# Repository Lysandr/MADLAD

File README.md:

# MADLAD
Modular Algorithm Demonstration Linux Autonomous Drone (MADLAD)

## What is this?
This is meant to be an open-source drone guidance, navigation, and control platform. The board is equipped with an MPU9260 (3ax accel, 3ax gyro, 3ax mag)
as well as an IMU380ZA, a single source time-of-flight lidar, and a barometer.  It has onboard 3.3V and 5V DC/DC converters. The brain is a
pocketbeagle computer.

Upgrades will be considered at a later time, this project is currently in a get-shit-done-asap stage.

## Goals for this project
* Get the flight computer board functioning.
* Get the PREEMPT_RT thread patch functioning in debian on the pocketbeagle
* Get a decent GNC framework implemented for plug and play algorithms based on a globally defined state machine

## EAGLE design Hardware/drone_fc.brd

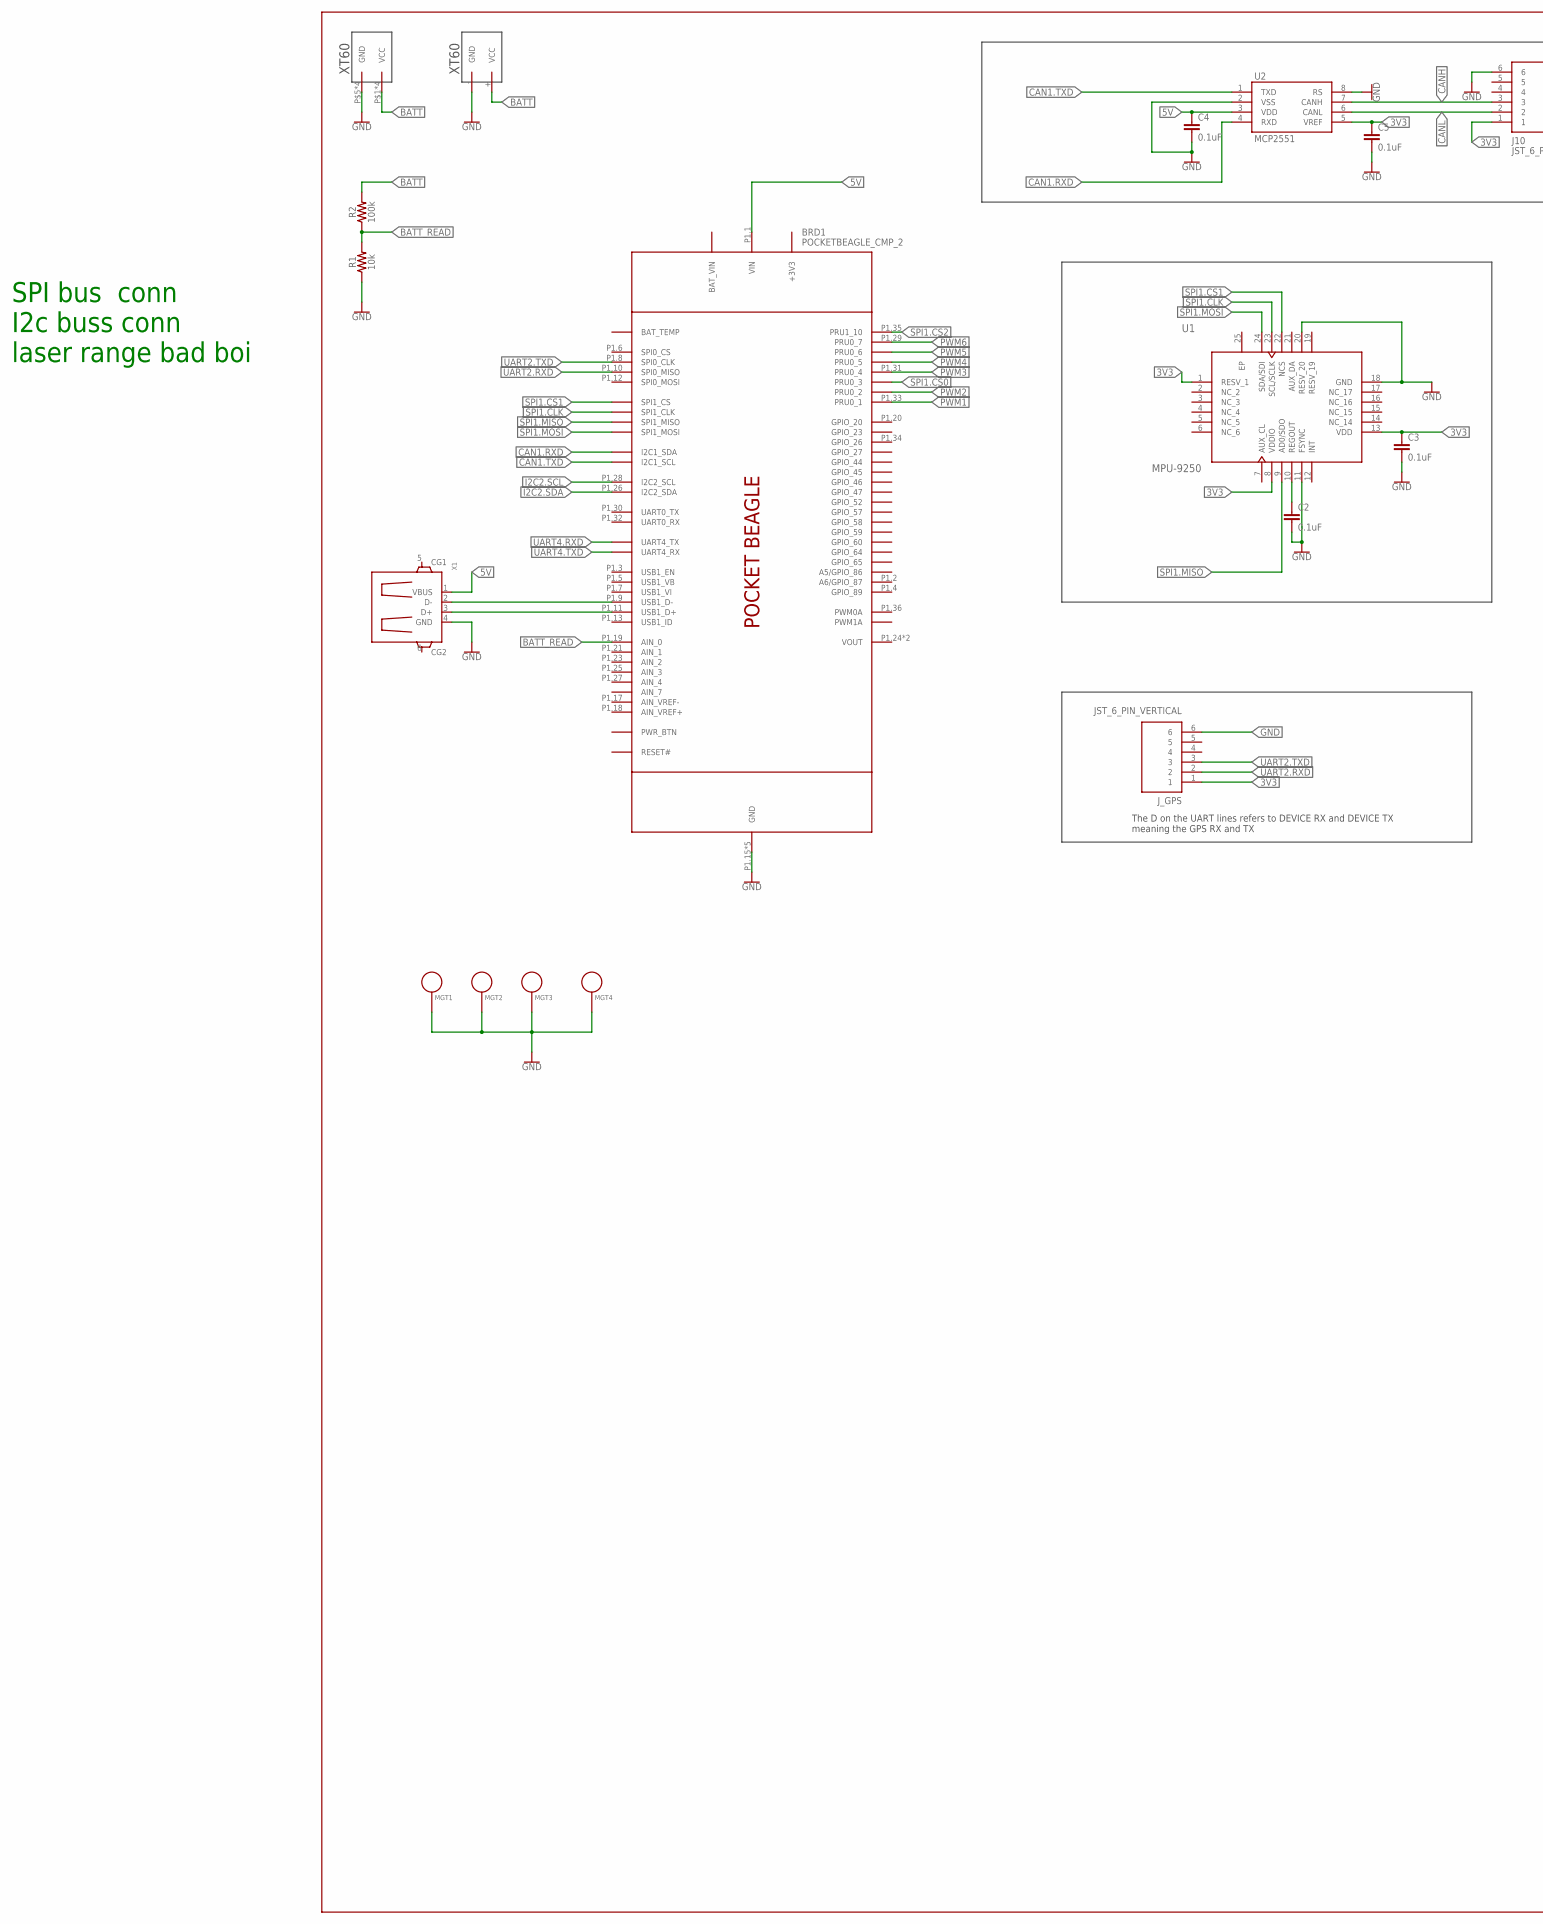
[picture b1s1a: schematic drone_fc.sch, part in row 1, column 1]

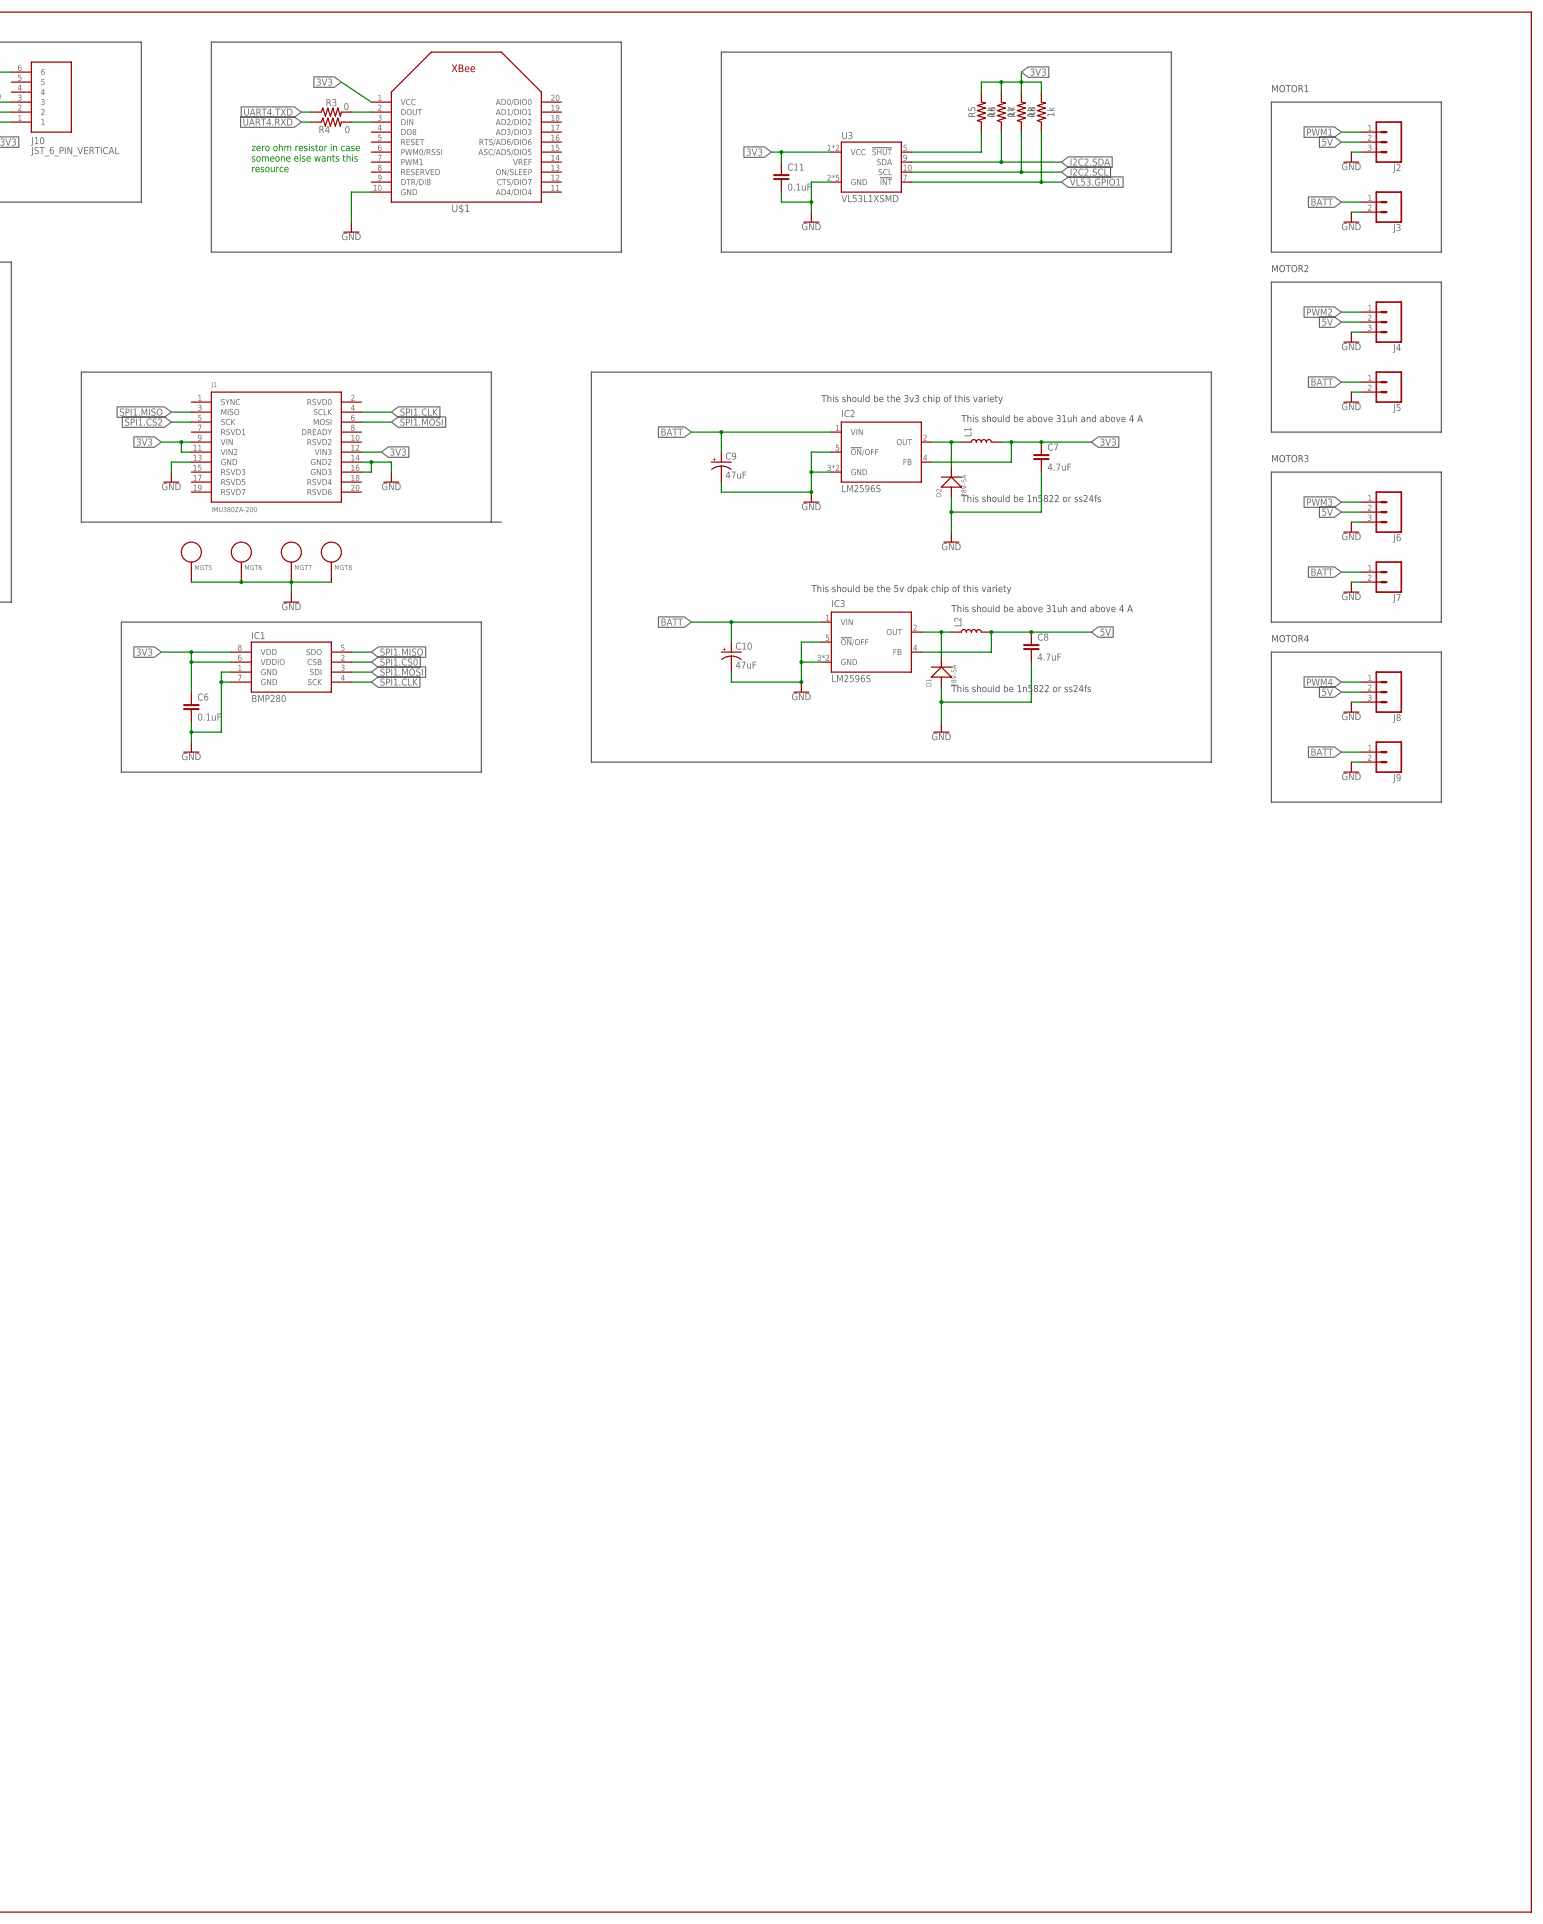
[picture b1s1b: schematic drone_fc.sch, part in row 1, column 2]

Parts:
BRD1: POCKETBEAGLE_CMP_2; POCKETBEAGLE_CMP
C2, C3, C4, C5, C6, C11: 0.1uF; 0603
C7, C8: 4.7uF; 1206
C9, C10: 47uF; PANASONIC_D
D1, D2: 28V-5A; DO-214AA
IC1: BMP280
IC2, IC3: LM2596S; TO263-5
J1: IMU380ZA-200; IMU380-CLM-110-02
J2, J4, J6, J8: CONN_03; 1X03
J3, J5, J7, J9: CONN_02PTH3; 1X02_LONGPADS
J10: JST_6_PIN_VERTICAL; JST-6-SMD-VERT-1.0MM
J_GPS: JST_6_PIN_VERTICAL; JST-6-SMD-VERT-1.0MM
L1, L2: 47µH/±30%/750mA; CR54
MGT1, MGT2, MGT3, MGT4, MGT5, MGT6, MGT7, MGT8: MOUNTING_HOLE; BEAGLEBONEBLACK_MOUNTING_HOLE
R1: 10k; 0603
R2: 100k; 0603
R3, R4: 0; 0603
R5, R6, R7, R8: 1k; 0603
U1: MPU-9250; 24-QFN
U2: MCP2551; SO08
U3: VL53L1XSMD; VL53L1X
U$1: XBEE
U$2: XT60_RA
U$3: XT60
X1: GHI2_USB_HOST_W/CHASSIS_GND; GHI2_USB_HOST_HORIZONTAL_W/CHASSIS_GND

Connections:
3V3: C3.1, C5.1, C6.1, C7.1, C11.1, IC1.6 (VDDIO), IC1.8 (VDD), IC2.4 (FB), J1.9 (VIN), J1.11 (VIN2), J1.12 (VIN3), J10.1, J_GPS.1, L1.P$2 (2), R5.2, R6.2, R7.2, R8.2, U1.1 (RESV_1), U1.8 (VDDIO), U1.13 (VDD), U2.5 (VREF), U3.1 (VCC), U3.11 (VCC), U$1.1 (VCC)
5V: BRD1.P1.1 (VIN), C4.1, C8.1, IC3.4 (FB), J2.2, J4.2, J6.2, J8.2, L2.P$2 (2), U2.3 (VDD), X1.1 (VBUS)
BATT: C9.+, C10.+, IC2.1 (VIN), IC3.1 (VIN), J3.1, J5.1, J7.1, J9.1, R2.2, U$2.P$1 (VCC), U$2.P$2 (VCC), U$2.P$3 (VCC), U$2.P$4 (VCC), U$3.+ (VCC)
BATT_READ: BRD1.P1.19 (AIN_0), R1.2, R2.1
CAN1.RXD: BRD1.P2.11 (I2C1_SDA), U2.4 (RXD)
CAN1.TXD: BRD1.P2.9 (I2C1_SCL), U2.1 (TXD)
CANH: J10.3, U2.7 (CANH)
CANL: J10.2, U2.6 (CANL)
EP: U1.25 (EP)
GND: BRD1.P1.15 (GND), BRD1.P1.16 (GND), BRD1.P1.22 (GND), BRD1.P2.15 (GND), BRD1.P2.21 (GND), C2.2, C3.2, C4.2, C5.2, C6.2, C7.2, C8.2, C9.-, C10.-, C11.2, D1.+, D2.+, IC1.1 (GND), IC1.7 (GND), IC2.3 (GND), IC2.5 (!ON!/OFF), IC2.6 (GND), IC3.3 (GND), IC3.5 (!ON!/OFF), IC3.6 (GND), J1.13 (GND), J1.14 (GND2), J1.16 (GND3), J2.3, J3.2, J4.3, J5.2, J6.3, J7.2, J8.3, J9.2, J10.6, J_GPS.6, MGT1.P$1, MGT2.P$1, MGT3.P$1, MGT4.P$1, MGT5.P$1, MGT6.P$1, MGT7.P$1, MGT8.P$1, R1.1, U1.11 (FSYNC), U1.18 (GND), U1.20 (RESV_20), U2.2 (VSS), U2.8 (RS), U3.2 (GND), U3.3 (GND), U3.4 (GND), U3.6 (GND), U3.12 (GND), U$1.10 (GND), U$2.P$5 (GND), U$2.P$6 (GND), U$2.P$7 (GND), U$2.P$8 (GND), U$3.- (GND), X1.4 (GND)
I2C2.SCL: BRD1.P1.28 (I2C2_SCL), R7.1, U3.10 (SCL)
I2C2.SDA: BRD1.P1.26 (I2C2_SDA), R6.1, U3.9 (SDA)
I2C2.SHUT: R5.1, U3.5 (!SHUT)
unnamed: C2.1, U1.10 (REGOUT)
unnamed: BRD1.P1.11 (USB1_D+), X1.3 (D+)
unnamed: BRD1.P1.9 (USB1_D-), X1.2 (D-)
unnamed: D2.-, IC2.2 (OUT), L1.P$1 (1)
unnamed: D1.-, IC3.2 (OUT), L2.P$1 (1)
unnamed: R3.2, U$1.2 (DOUT)
unnamed: R4.2, U$1.3 (DIN)
PWM1: BRD1.P1.33 (PRU0_1), J2.1
PWM2: BRD1.P2.32 (PRU0_2), J4.1
PWM3: BRD1.P1.31 (PRU0_4), J6.1
PWM4: BRD1.P2.34 (PRU0_5), J8.1
PWM5: BRD1.P2.28 (PRU0_6)
PWM6: BRD1.P1.29 (PRU0_7)
SPI1.CLK: BRD1.P2.29 (SPI1_CLK), IC1.4 (SCK), J1.4 (SCLK), U1.23 (SCL/SCLK)
SPI1.CS0: BRD1.P2.30 (PRU0_3), IC1.2 (CSB)
SPI1.CS1: BRD1.P2.31 (SPI1_CS), U1.22 (NCS)
SPI1.CS2: BRD1.P1.35 (PRU1_10), J1.5 (SCK)
SPI1.MISO: BRD1.P2.27 (SPI1_MISO), IC1.5 (SDO), J1.3 (MISO), U1.9 (AD0/SDO)
SPI1.MOSI: BRD1.P2.25 (SPI1_MOSI), IC1.3 (SDI), J1.6 (MOSI), U1.24 (SDA/SDI)
UART2.RXD: BRD1.P1.10 (SPI0_MISO), J_GPS.2
UART2.TXD: BRD1.P1.8 (SPI0_CLK), J_GPS.3
UART4.RXD: BRD1.P2.7 (UART4_TX), R4.1
UART4.TXD: BRD1.P2.5 (UART4_RX), R3.1
VL53.GPIO1: R8.1, U3.7 (!INT)

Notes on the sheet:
SPI bus conn I2c buss conn laser range bad boi
MOTOR1
MOTOR2
MOTOR3
MOTOR4
The D on the UART lines refers to DEVICE RX and DEVICE TX meaning the GPS RX and TX
This should be 1n5822 or ss24fs
This should be above 31uh and above 4 A
This should be the 3v3 chip of this variety
This should be the 5v dpak chip of this variety
zero ohm resistor in case someone else wants this resource

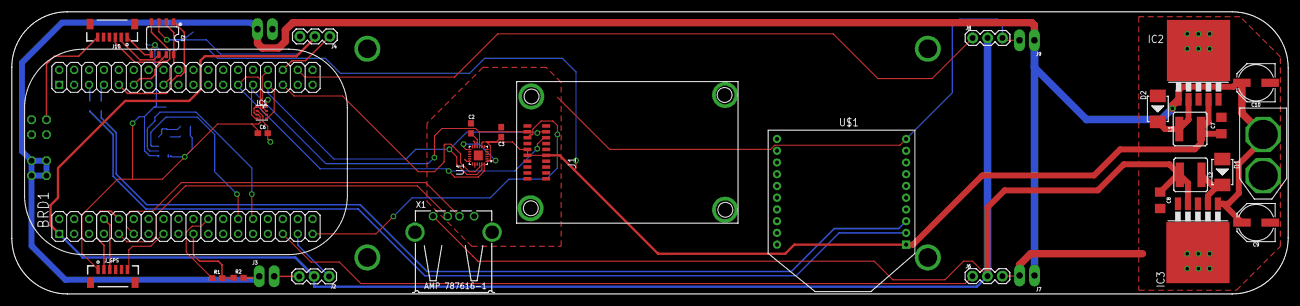
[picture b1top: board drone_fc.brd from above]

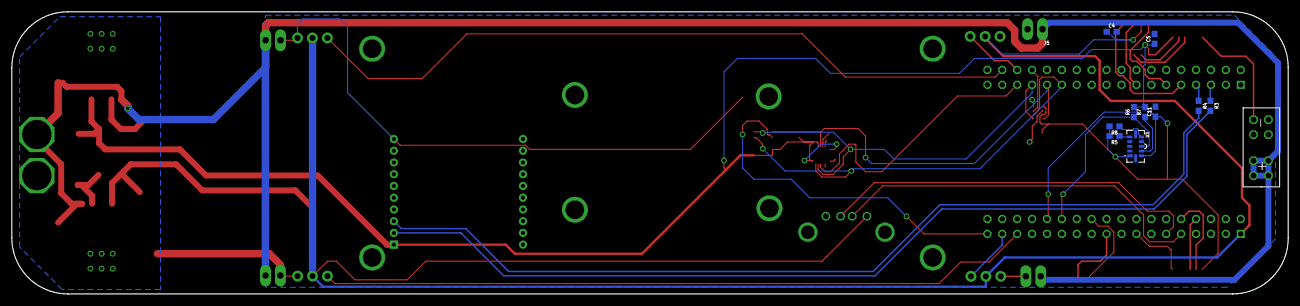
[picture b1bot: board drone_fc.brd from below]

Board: 2 copper layers, 217.5 x 48.1 mm, 52 parts (12 on the bottom side), 34 nets.

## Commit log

2020-01-01 init hardware design repo
2020-01-11 updating some shit
2020-01-11 adding pin configs
2020-01-11 pin config giles
2020-01-14 update post verbier

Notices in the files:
parts and their libraries:
SparkFun-Connectors: Licensing: Creative Commons ShareAlike 4.0 International - https://creativecommons.org/licenses/by-sa/4.0
